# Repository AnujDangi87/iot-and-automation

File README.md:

# iot-and-automation
<h1>Repo for IOT and automation projects.</h1>
<h3>Each project contains its schematics file and pcb design layout along with its embedded C/C++ and arduino codes Or python/microPython in Raspberry pi pico</h3>
<h4>All this projects are done in kiCad</h4>

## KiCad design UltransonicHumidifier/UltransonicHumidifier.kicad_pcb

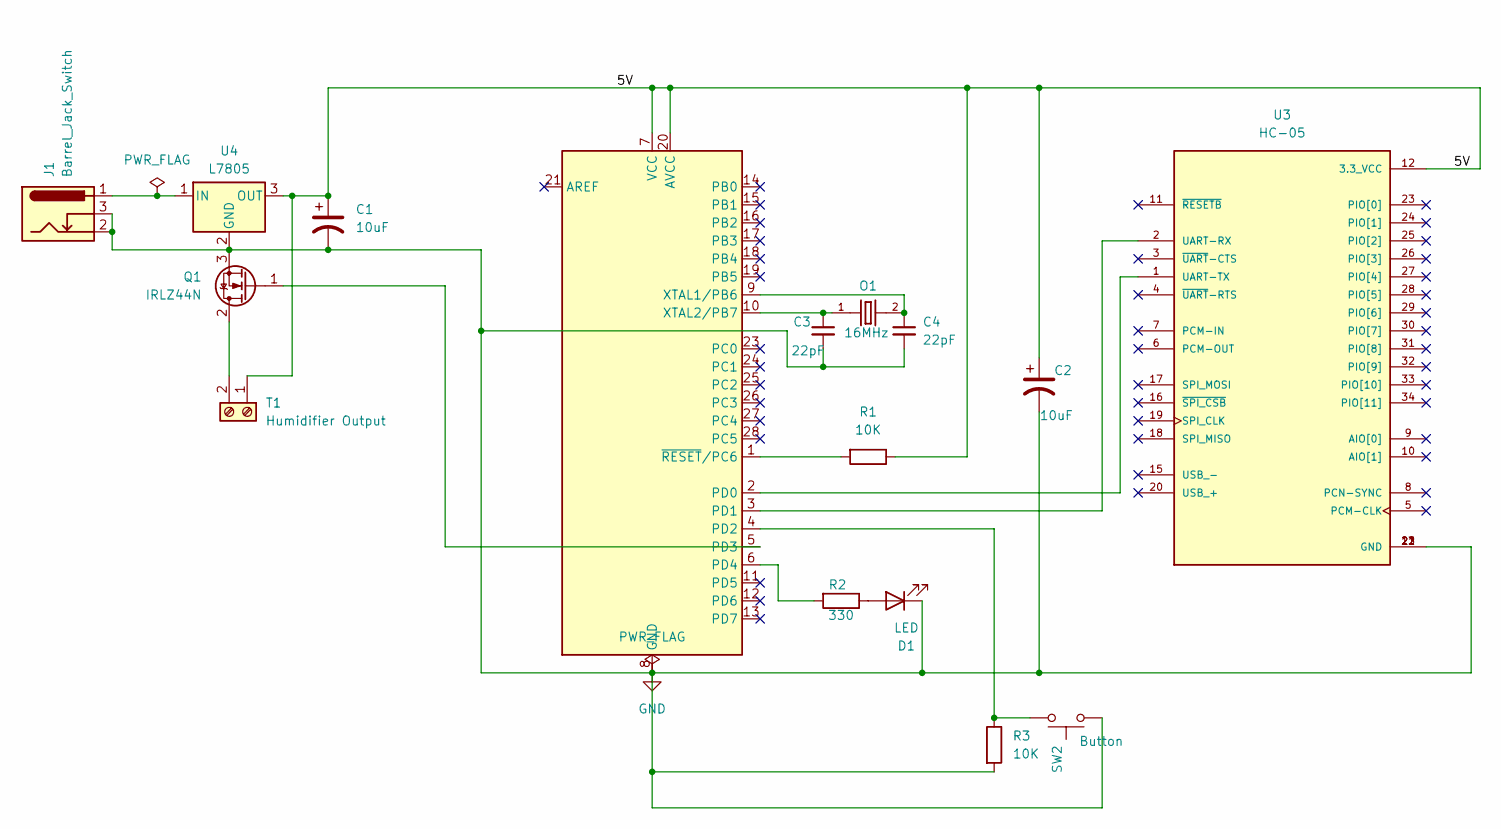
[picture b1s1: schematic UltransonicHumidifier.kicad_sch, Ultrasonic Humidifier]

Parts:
C1, C2: 10uF; CP_Radial_D10.0mm_P7.50mm
C3, C4: 22pF; C_Disc_D11.0mm_W5.0mm_P5.00mm
D1: LED; LED_D3.0mm
J1: Barrel_Jack_Switch; BarrelJack_Horizontal
O1: 16MHz; XTAL_ECS-160-20-4-DN
Q1: IRLZ44N; TO-220-3_Vertical
R1, R3: 10K; R_Axial_DIN0207_L6.3mm_D2.5mm_P7.62mm_Horizontal
R2: 330; R_Axial_DIN0207_L6.3mm_D2.5mm_P7.62mm_Horizontal
SW2: Button; SW_PUSH_6mm
T1: Humidifier Output; TerminalBlock_bornier-2_P5.08mm
U1: ATmega328-P; DIP-28_W7.62mm
U3: HC-05; XCVR_HC-05; PARTREV v1.0
U4: L7805; TO255P1020X450X2000-3

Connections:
/5V: C1.1, C2.1, R1.1, T1.1, U1.7 (VCC), U1.20 (AVCC), U3.12 (3.3_VCC), U4.3 (OUT)
GND: C1.2, C2.2, C3.2, C4.2, D1.1 (K), J1.2, J1.3, Q1.3 (S), R3.2, SW2.2, U1.8 (GND), U1.22 (GND), U3.13 (GND), U3.21 (GND), U3.22 (GND), U4.2 (GND)
unnamed: D1.2 (A), R2.1
unnamed: Q1.2 (D), T1.2
unnamed: Q1.1 (G), U1.5 (PD3)
unnamed: U1.2 (PD0), U3.1 (UART-TX)
unnamed: U1.3 (PD1), U3.2 (UART-RX)
unnamed: R3.1, SW2.1, U1.4 (PD2)
unnamed: R2.2, U1.6 (PD4)
unnamed: C4.1, O1.2, U1.9 (XTAL1/PB6)
unnamed: C3.1, O1.1, U1.10 (XTAL2/PB7)
unnamed: R1.2, U1.1 (~RESET/PC6)
unnamed: J1.1, U4.1 (IN)

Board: 2 copper layers, 19 parts (0 on the bottom side), 15 nets, no tracks yet.

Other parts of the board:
C3#2, C4#2: 10uF; C_Radial_D5.0mm_H11.0mm_P2.00mm
U2: AMS1117-5.0; SOT-223-3_TabPin2

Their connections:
unnamed: C3#2.2, C4#2.2
unnamed: C3#2.1, C4#2.1

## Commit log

2025-05-28 Adding smart humidifier
2025-06-03 Adding initials of UniversalRemote using microcontroller with ir led
